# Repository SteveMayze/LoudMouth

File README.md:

# LoudMouth
The Audio Amplifier module for the Roll With it Project.

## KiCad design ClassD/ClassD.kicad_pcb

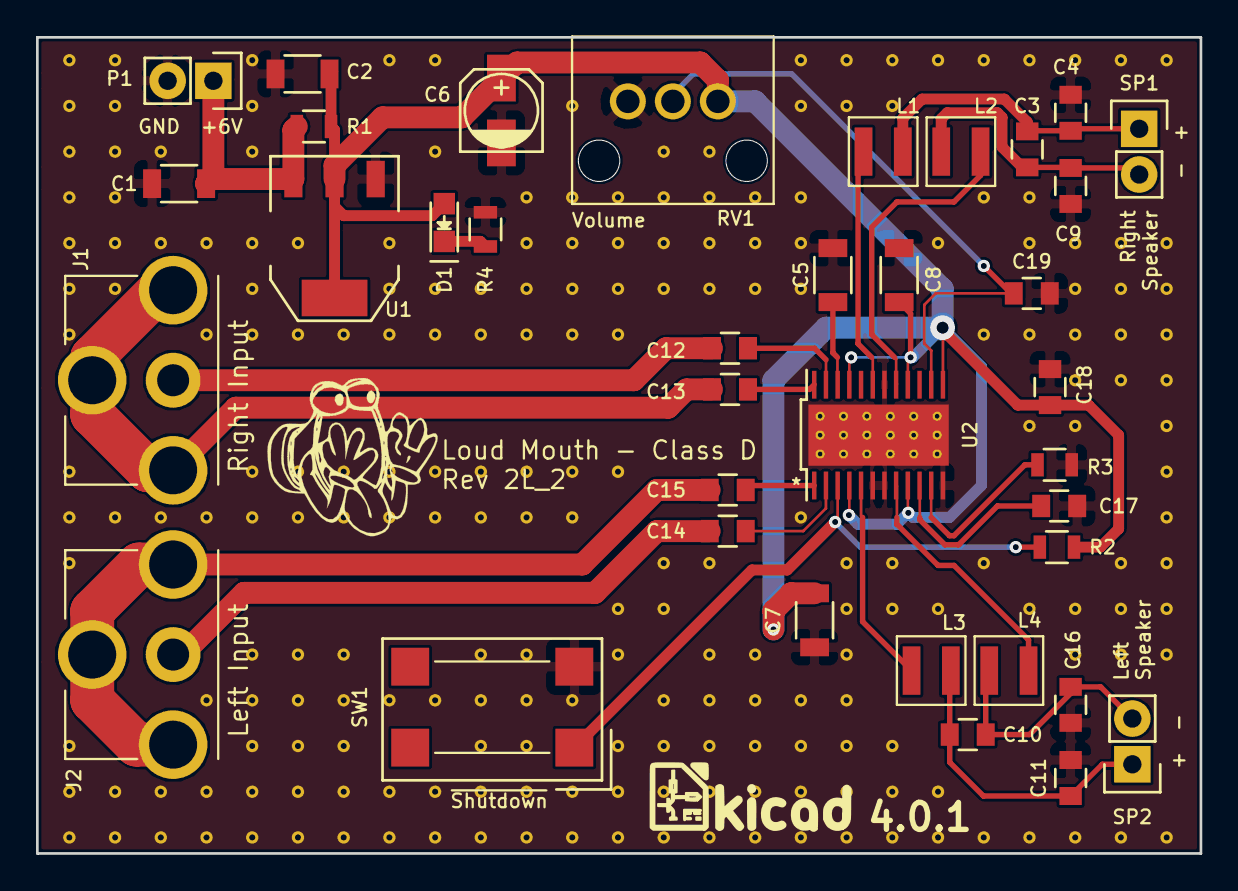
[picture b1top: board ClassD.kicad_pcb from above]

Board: 2 copper layers, 64.6 x 45.3 mm, 261 parts (0 on the bottom side), 25 nets.

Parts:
C1, C2: 4.7 μF; C_1206
C3, C10: 470 nF; C_0805
C4, C9, C11, C12, C13, C14, C15, C16: 0.1 μF; C_0805
C5, C7, C8: 1 μF; C_1206
C6: 10 μF; c_elec_4x5.3
C17: 220 pF; C_0805
C18: 1 μF; C_0805
C19: NO-POP; C_0805
D1: LED; LED_0805
J1, J2: RCJ-01X
L1, L2, L3, L4: 33 μΗ; SRN3051
LOGO1: LoudMouth_10; LoudMouth_Logo_10
LOGO2: KiCad; KiCad-Logo
P1: CONN_01X02; Pin_Header_Straight_1x02
R1: NOPOP; R_0805
R2, R3: 120 kΩ; R_0805
R4: 470Ω; R_0805
RV1: 50 kΩ; EVUE-POT
SP1, SP2: 8 Ω; Pin_Header_Straight_1x02
ST**1111111, ST**1111112, ST**1111113, ST**1111114, ST**1111115, ST**1111116, ST**1111117, ST**1111121, ST**1111122, ST**1111123, ST**1111124, ST**1111125, ST**1111126, ST**1111134, ST**1111135, ST**1111145, ST**1111147, ST**1111151, ST**1111152, ST**1111153, ST**1111155, ST**1111156, ST**1111157, ST**1111165, ST**1111167, ST**1111177, ST**1111181, ST**1111185, ST**1111186, ST**1111187, ST**1111191, ST**1111193, ST**1111196, ST**1111197, ST**11111106, ST**11111107, ST**11111110, ST**11111111, ST**11111112, ST**11111114, ST**11111115, ST**11111116, ST**11111116#2, ST**11111117, ST**11111117#2, ST**11111118, ST**11111122, ST**11111124, ST**11111125, ST**11111126, ST**11111127, ST**11111134, ST**11111135, ST**11111136, ST**11111137, ST**11111143, ST**11111144, ST**11111145, ST**11111146, ST**11111153, ST**11111154, ST**11111155, ST**11111156, ST**11111164, ST**11111165, ST**11111166, ST**11111171, ST**11111172, ST**11111174, ST**11111175, ST**11111176, ST**11111205, ST**11111211, ST**11111217, ST**11111217#2, ST**11111218, ST**11111221, ST**11111224, ST**11111225, ST**11111225#2, ST**11111227, ST**11111229, ST**11111231, ST**11111235, ST**11111236, ST**11111237, ST**11111238, ST**11111239, ST**11111241, ST**11111245, ST**11111246, ST**11111247, ST**11111248, ST**11111251, ST**11111255, ST**11111256, ST**11111257, ST**11111258, ST**11111259, ST**11111311, ST**11111317, ST**11111318, ST**11111411, ST**11111415, ST**11111417, ST**11111418, ST**11111510, ST**11111511, ST**11111514, ST**11111515, ST**11111516, ST**11111517, ST**11111518, ST**11111610, ST**11111611, ST**11111614, ST**11111615, ST**11111616, ST**11111617, ST**11111618, ST**11111710, ST**11111711, ST**11111714, ST**11111715, ST**11111716, ST**11111717, ST**11111718, ST**11111810, ST**11111811, ST**11111815, ST**11111817, ST**11111818, ST**11111910, ST**11111911, ST**11111915, ST**11111917, ST**11111918, ST**111111010, ST**111111011, ST**111111014, ST**111111015, ST**111111016, ST**111111017, ST**111111018, ST**111111110, ST**111111111, ST**111111114, ST**111111115, ST**111111116, ST**111111117, ST**111111118, ST**111111210, ST**111111211, ST**111111215, ST**111111217, ST**111111218, ST**111111310, ST**111111313, ST**111111314, ST**111111316, ST**111111317, ST**111111318, ST**111111412, ST**111111413, ST**111111415, ST**111111416, ST**111111417, ST**111111418, ST**111111512, ST**111111514, ST**111111515, ST**111111516, ST**111111517, ST**111111518, ST**111111614, ST**111111615, ST**111111616, ST**111111617, ST**111111618, ST**111111711, ST**111111715, ST**111111716, ST**111111717, ST**111111718, ST**111111811, ST**111111812, ST**111111812#2, ST**111111813, ST**111111814, ST**111111815, ST**111111816, ST**111111817, ST**111111818, ST**111111822, ST**111111912, ST**111111913, ST**111111916, ST**111111917, ST**111111918, ST**111112013, ST**111112017, ST**111112018, ST**111112112, ST**111112118, ST**111112213, ST**111112218, ST**111112313, ST**111112314, ST**111112318, ST**111112412, ST**111112413, ST**111112414, ST**111112418, ST**111112510, ST**111112511, ST**111112512, ST**111112513, ST**111112514, ST**111112518, ST**1111118211, ST**1111118221, ST**1111118231: Stitch_VIA
SW1: FSM2JSMAA
U1: AP1117E50G-13; SOT-223
U2: TPA2008D2; 24-TSSOP-PowerPad

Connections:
/BYPASS: C5.2, U2.22
/LIN+: C14.2, J2.2
/LIN-: C15.2, J2.1
/LOUT+: C10.2, C11.2, L3.2, SP2.1
/LOUT-: C10.1, C16.2, L4.2, SP2.2
/LOUTN: L4.1, U2.8
/LOUTP: L3.1, U2.5
/RIN+: C12.2, J1.2
/RIN-: C13.2, J1.1
/ROUT+: C3.2, C4.2, L1.2, SP1.1
/ROUT-: C3.1, C9.2, L2.2, SP1.2
/ROUTN: L2.1, U2.17
/ROUTP: L1.1, U2.19
/VDD: C2.2, C6.1, C7.2, C8.2, C18.2, D1.2, R1.1, R2.1, RV1.1, U1.2, U1.4, U2.4, U2.9, U2.13, U2.16, U2.21
/VIN: C1.2, P1.1, R1.2, U1.3
/VOLUME: C19.2, RV1.2, U2.14
/~SHUTDOWN: R2.2, SW1.1, U2.3
GND: C1.1, C2.1, C4.1, C5.1, C6.2, C7.1, C8.1, C9.1, C11.1, C16.1, C17.2, C18.1, C19.1, P1.2, R3.2, R4.2, RV1.3, ST**1111111.1, ST**1111112.1, ST**1111113.1, ST**1111114.1, ST**1111115.1, ST**1111116.1, ST**1111117.1, ST**1111121.1, ST**1111122.1, ST**1111123.1, ST**1111124.1, ST**1111125.1, ST**1111126.1, ST**1111134.1, ST**1111135.1, ST**1111145.1, ST**1111147.1, ST**1111151.1, ST**1111152.1, ST**1111153.1, ST**1111155.1, ST**1111156.1, ST**1111157.1, ST**1111165.1, ST**1111167.1, ST**1111177.1, ST**1111181.1, ST**1111185.1, ST**1111186.1, ST**1111187.1, ST**1111191.1, ST**1111193.1, ST**1111196.1, ST**1111197.1, ST**11111106.1, ST**11111107.1, ST**11111110.1, ST**11111111.1, ST**11111112.1, ST**11111114.1, ST**11111115.1, ST**11111116.1, ST**11111116#2.1, ST**11111117.1, ST**11111117#2.1, ST**11111118.1, ST**11111122.1, ST**11111124.1, ST**11111125.1, ST**11111126.1, ST**11111127.1, ST**11111134.1, ST**11111135.1, ST**11111136.1, ST**11111137.1, ST**11111143.1, ST**11111144.1, ST**11111145.1, ST**11111146.1, ST**11111153.1, ST**11111154.1, ST**11111155.1, ST**11111156.1, ST**11111164.1, ST**11111165.1, ST**11111166.1, ST**11111171.1, ST**11111172.1, ST**11111174.1, ST**11111175.1, ST**11111176.1, ST**11111205.1, ST**11111211.1, ST**11111217.1, ST**11111217#2.1, ST**11111218.1, ST**11111221.1, ST**11111224.1, ST**11111225.1, ST**11111225#2.1, ST**11111227.1, ST**11111229.1, ST**11111231.1, ST**11111235.1, ST**11111236.1, ST**11111237.1, ST**11111238.1, ST**11111239.1, ST**11111241.1, ST**11111245.1, ST**11111246.1, ST**11111247.1, ST**11111248.1, ST**11111251.1, ST**11111255.1, ST**11111256.1, ST**11111257.1, ST**11111258.1, ST**11111259.1, ST**11111311.1, ST**11111317.1, ST**11111318.1, ST**11111411.1, ST**11111415.1, ST**11111417.1, ST**11111418.1, ST**11111510.1, ST**11111511.1, ST**11111514.1, ST**11111515.1, ST**11111516.1, ST**11111517.1, ST**11111518.1, ST**11111610.1, ST**11111611.1, ST**11111614.1, ST**11111615.1, ST**11111616.1, ST**11111617.1, ST**11111618.1, ST**11111710.1, ST**11111711.1, ST**11111714.1, ST**11111715.1, ST**11111716.1, ST**11111717.1, ST**11111718.1, ST**11111810.1, ST**11111811.1, ST**11111815.1, ST**11111817.1, ST**11111818.1, ST**11111910.1, ST**11111911.1, ST**11111915.1, ST**11111917.1, ST**11111918.1, ST**111111010.1, ST**111111011.1, ST**111111014.1, ST**111111015.1, ST**111111016.1, ST**111111017.1, ST**111111018.1, ST**111111110.1, ST**111111111.1, ST**111111114.1, ST**111111115.1, ST**111111116.1, ST**111111117.1, ST**111111118.1, ST**111111210.1, ST**111111211.1, ST**111111215.1, ST**111111217.1, ST**111111218.1, ST**111111310.1, ST**111111313.1, ST**111111314.1, ST**111111316.1, ST**111111317.1, ST**111111318.1, ST**111111412.1, ST**111111413.1, ST**111111415.1, ST**111111416.1, ST**111111417.1, ST**111111418.1, ST**111111512.1, ST**111111514.1, ST**111111515.1, ST**111111516.1, ST**111111517.1, ST**111111518.1, ST**111111614.1, ST**111111615.1, ST**111111616.1, ST**111111617.1, ST**111111618.1, ST**111111711.1, ST**111111715.1, ST**111111716.1, ST**111111717.1, ST**111111718.1, ST**111111811.1, ST**111111812.1, ST**111111812#2.1, ST**111111813.1, ST**111111814.1, ST**111111815.1, ST**111111816.1, ST**111111817.1, ST**111111818.1, ST**111111822.1, ST**111111912.1, ST**111111913.1, ST**111111916.1, ST**111111917.1, ST**111111918.1, ST**111112013.1, ST**111112017.1, ST**111112018.1, ST**111112112.1, ST**111112118.1, ST**111112213.1, ST**111112218.1, ST**111112313.1, ST**111112314.1, ST**111112318.1, ST**111112412.1, ST**111112413.1, ST**111112414.1, ST**111112418.1, ST**111112510.1, ST**111112511.1, ST**111112512.1, ST**111112513.1, ST**111112514.1, ST**111112518.1, ST**1111118211.1, ST**1111118221.1, ST**1111118231.1, SW1.3, U1.1, U2.6, U2.7, U2.12, U2.18, U2.25
unnamed: C12.1, U2.23
unnamed: C13.1, U2.24
unnamed: C14.1, U2.2
unnamed: C15.1, U2.1
unnamed: C17.1, U2.10
unnamed: D1.1, R4.1
unnamed: R3.1, U2.11

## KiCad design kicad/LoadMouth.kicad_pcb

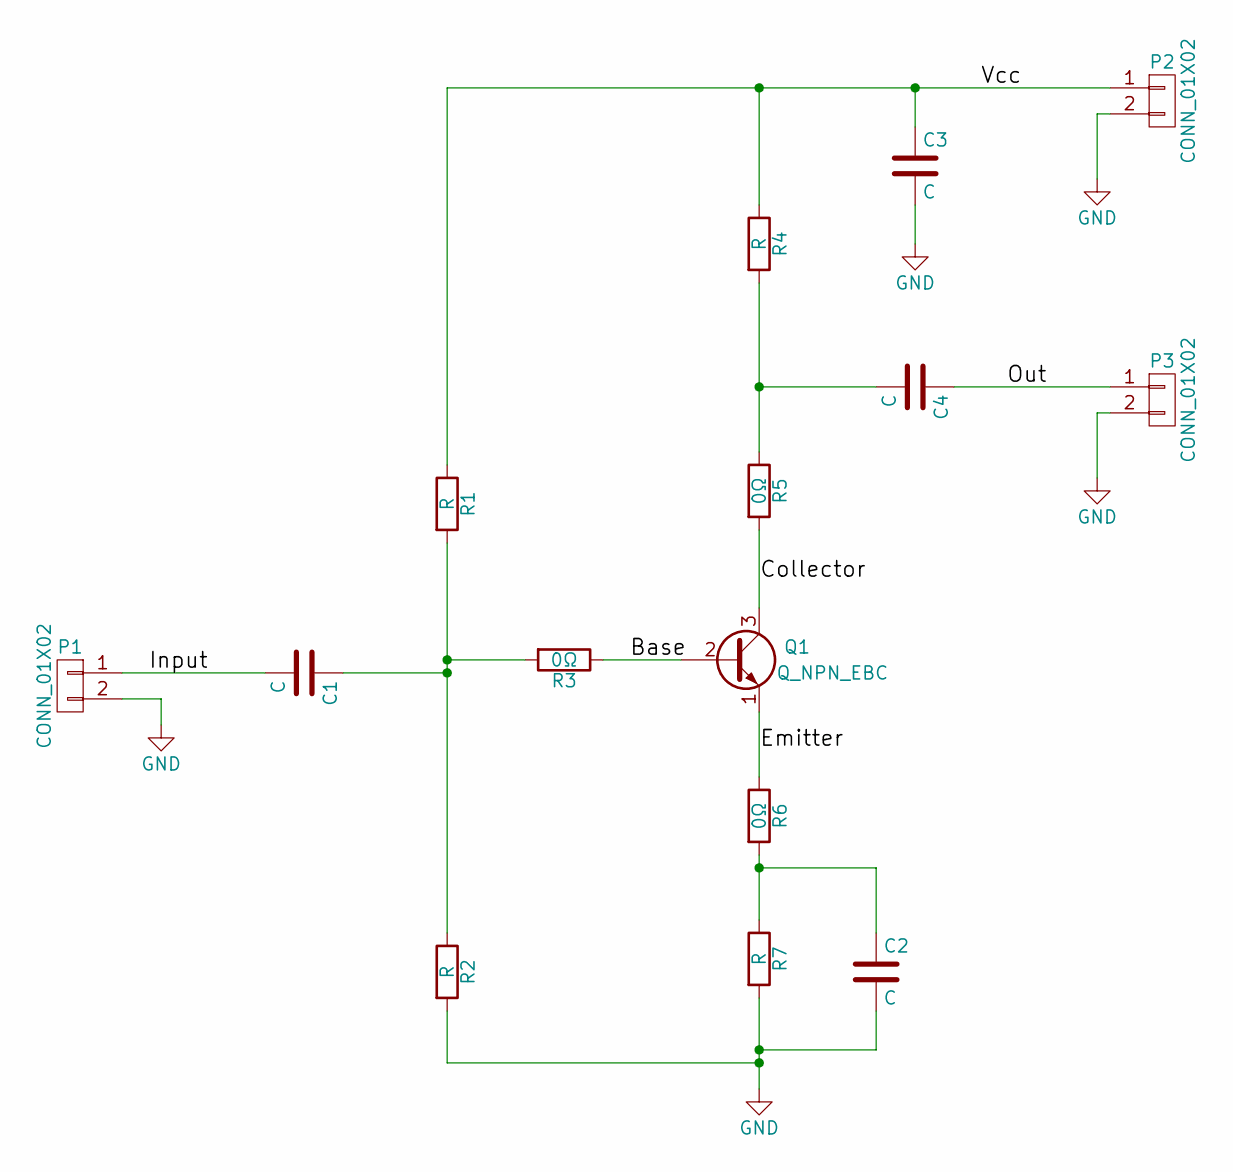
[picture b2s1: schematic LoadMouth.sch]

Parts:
C1, C2, C3, C4: C; C_1210_HandSoldering
P1, P2, P3: CONN_01X02; Pin_Header_Straight_1x02
Q1: Q_NPN_EBC; TO-92_Molded_Narrow
R1, R2, R4, R7: R; R_0805_HandSoldering
R3, R5, R6: 0Ω; R_0805_HandSoldering

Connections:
/Base: Q1.2 (B), R3.1
/Collector: Q1.3 (C), R5.2
/Emitter: Q1.1 (E), R6.1
/Input: C1.2, P1.1
/Out: C4.1, P3.1
/Vcc: C3.1, P2.1, R1.1, R4.1
GND: C2.2, C3.2, P1.2, P2.2, P3.2, R2.2, R7.2
unnamed: C1.1, R1.2, R2.1, R3.2
unnamed: C2.1, R6.2, R7.1
unnamed: C4.2, R4.2, R5.1

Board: 2 copper layers, 15 parts (0 on the bottom side), 10 nets, no tracks yet.

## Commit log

2015-08-31 Added spice model for the A-Class amplifier
2015-09-17 Initial project and schematic
2015-09-17 Started layout
2015-09-18 Finalised the layout and created the Gerbers
2015-11-15 Added values for parts
2016-02-06 Altered the directory structure and added the intitial schematic for the Class-D
2016-02-07 Updated the schematic with some part numbers and parametrics
2016-02-07 Updated the BOM specifications and added a regulator for VDD
2016-02-08 Updated the digikey part numbers etc.
2016-02-09 Updated the speaker with the link to digi-key
2016-02-09 Changed the voltage regulator to 1A (for the 4Ohm case)
2016-02-10 Updated speaker specs
2016-06-28 Started associating footprints to symbols and checking own stock
2016-07-02 Added some documentation
2016-07-02 Started the layout
2016-07-03 Added the GND Zones and started routing
2016-07-03 Added a reference layout as overlays
2016-07-03 updated the layout
2016-07-04 Added the LM-D logo
2016-07-04 Wrapping up the routing
2016-07-04 Added the logos and revision text
2016-07-04 Fininalised the logos
2016-07-04 Stitched the ground planes
2016-07-05 Updated the layout with some circuit changes as well as the audio chip footprint.
2016-07-06 Added annotation to the AGND wire
2016-07-07 Small reference placement
2016-07-11 Complted the gerbers and sent to OSHPark
2016-08-16 Correction to solder mask and 24-TSSOP power Pad
2016-08-16 Revision 2L_2 Gerbers created
